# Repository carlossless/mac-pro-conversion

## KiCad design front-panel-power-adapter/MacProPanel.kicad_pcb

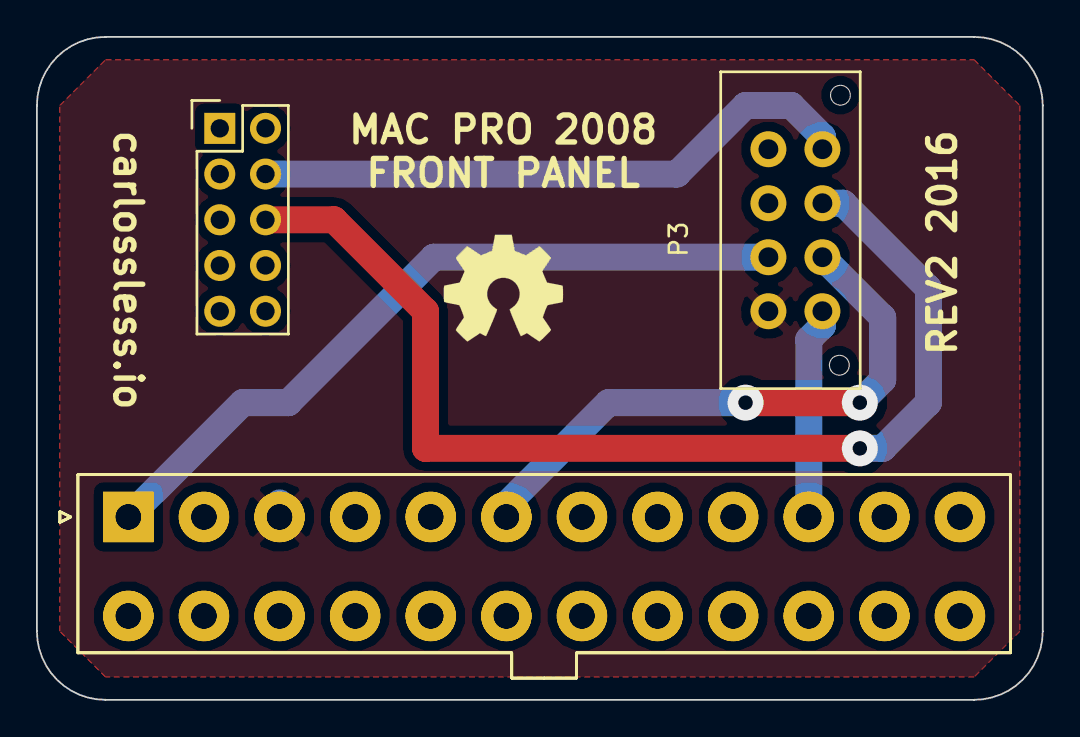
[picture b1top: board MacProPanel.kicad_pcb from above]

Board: 2 copper layers, 55.9 x 36.8 mm, 4 parts (0 on the bottom side), 26 nets.

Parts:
P3: CONN_02X04; Molex_Microfit3_Header_02x04_Straight_43045-0828
P4: CONN_02X05; Pin_Header_Straight_2x05
P7, P8: CONN_02X12; Molex_MiniFit-JR-5556-24A_2x12x4.20mm_Straight

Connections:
ATX01_3.3V: P3.2, P7.1, P8.1
ATX02: P7.2, P8.2
ATX04: P7.4, P8.4
ATX06_5V: P3.6, P7.6, P8.6
ATX08: P7.8, P8.8
ATX10_12V: P3.5, P7.10, P8.10
ATX12: P7.12, P8.12
ATX14: P7.14, P8.14
ATX16: P7.16, P8.16
ATX18: P7.18, P8.18
ATX20: P7.20, P8.20
ATX22: P7.22, P8.22
ATX24: P7.24, P8.24
ATX_05: P7.5, P8.5
ATX_07: P7.7, P8.7
ATX_09: P7.9, P8.9
ATX_11: P7.11, P8.11
ATX_13: P7.13, P8.13
ATX_15: P7.15, P8.15
ATX_17: P7.17, P8.17
ATX_19: P7.19, P8.19
ATX_21: P7.21, P8.21
ATX_23: P7.23, P8.23
GND: P3.1, P7.3, P8.3
MB_MSG-: P3.8, P4.4
MB_PW+: P3.7, P4.6

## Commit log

2016-09-28 Added front panel schematics
2016-10-13 Fron Panel Nanofit connector exchanged with microfit3
2016-10-16 Front Panel Usb Adapter & Cleanup
2016-10-17 SATA Power Adapter Schema. No PCB
